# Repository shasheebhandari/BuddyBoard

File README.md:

Buddy Board

**Background**

When i was a kind my dad bought me one buddy toy , it had a screen , and a speaker that used to be activated when it was shaken . I was deeply connected to that toy but it got damaged later and i couldn't repair it . So In this project i have tried to re create that toy which used to display animation in idle but when shaken it used to show time . I am making this project to revive my childhood's fav toy buddy .

**Overview**

Buddy Board is a compact, ESP32-S3-based development board designed for projects requiring multi-USB connectivity, onboard sensing, and power management. The board integrates USB-C interfaces, an OLED display, motion and environmental sensors, and regulated power rails for both battery and USB-powered operation.

The design targets small-scale IoT or embedded applications where data acquisition, display, and connectivity need to coexist within a single board.

---

## Features
- **Microcontroller:** ESP32-S3-WROOM-1 with integrated WiFi and Bluetooth  
- **Display:** SSD1306 0.96" OLED module  
- **Sensors:**
  - BME680 (Gas, Temperature, Humidity, Pressure)
  - MPU-6000 (6-axis Accelerometer + Gyroscope)
- **USB Connectivity:**
  - 1x Upstream USB-C port (data and power input)
  - 2x Downstream USB-C ports (power and peripheral extension)
- **Power Management:**
  - TP4056-based Li-ion charging circuit
  - XL1509-3.3 buck converter for regulated 3.3V output
  - Screw terminal for external power or battery input
- **Indicator & Protection:**
  - SS34 Schottky diodes for reverse-current protection
  - Bypass and decoupling capacitors for power stability  

---

## Design Specifications
| Category | Specification |
|-----------|----------------|
| **MCU** | ESP32-S3-WROOM-1 |
| **Input Voltage** | 5V via USB or screw terminal |
| **Regulated Output** | 3.3V (via XL1509) |
| **Charging IC** | TP4056-42 ESOP8 |
| **Display Interface** | I²C (SDA, SCL) |
| **Sensor Interface** | I²C shared bus |
| **Board Layers** | 4 (Top, GND, Power, Bottom) |
| **Mounting** | Standard headers and terminal block |
| **Design Software** | KiCad 9 |

---

## File Contents
| File | Description |
|------|--------------|
| `.pro` | KiCad project file |
| `.sch` | Schematic diagram |
| `.pcb` | PCB layout |
| `.bom` | Bill of Materials |
| `.wrl` | 3D model (board visualization) |

---

## Component Summary (BOM)
| Reference | Qty | Component | Description |
|------------|-----|------------|--------------|
| U1 | 1 | ESP32-S3-WROOM-1 | Main processor |
| U2 | 1 | MPU-6000 | Motion sensor |
| U3 | 1 | XL1509-3.3 | Buck regulator |
| U4 | 1 | BME680 | Environmental sensor |
| U5 | 1 | TP4056-42 | Li-ion charger |
| D1, D3 | 2 | SS34 | Schottky diodes |
| J1, J2 | 2 | USB-C (Downstream) | Peripheral connections |
| J3 | 1 | USB-C (Upstream) | Power and data input |
| J4 | 1 | Screw terminal | External power input |
| C1–C4 | 4 | Capacitors | Power filtering |
| R1–R4 | 4 | Resistors | Pull-ups / current limiting |
| Brd1 | 1 | SSD1306 | OLED display module |

Full component details including footprints and datasheets are available in the included BOM file.

---

## Electrical Design Overview

### Power Distribution
- **5V Input:** Received from upstream USB-C or screw terminal.  
- **Voltage Regulation:** 5V stepped down to 3.3V via **XL1509-3.3** for logic and sensors.  
- **Battery Charging:** **TP4056** manages Li-ion charging when external power is available.  
- **Diode Protection:** **SS34 diodes** prevent reverse current between power sources.  

### Communication Buses
- **I²C Bus:**  
  Shared between ESP32-S3, SSD1306, BME680, and MPU-6000.  
  SDA and SCL lines routed with balanced lengths and pull-up resistors.  

- **USB Data Lines:**  
  Upstream USB carries data to ESP32-S3; downstream ports provide peripheral connectivity and power distribution.  

---

## PCB Design and Layout
- **Layer Stack:**  
  1. Top Layer — Signal routing and components  
  2. Inner Layer 1 — Dedicated Ground Plane  
  3. Inner Layer 2 — 5V and 3.3V Power Plane  
  4. Bottom Layer — Secondary signal routing  

- **Grounding:**  
  Solid ground plane with multiple stitching vias for signal integrity.  

- **Routing Strategy:**  
  - Differential routing for USB data pairs  
  - Short, wide traces for power lines  
  - Decoupling capacitors placed near IC supply pins  

---

## Assembly Notes
1. Open project in **KiCad 9** and verify all footprints before manufacturing.  
2. Use **4-layer PCB fabrication** (1.6mm FR4, 1oz copper recommended).  
3. Solder **SMD components** first (U1–U5, D1–D3).  
4. Solder **through-hole components** and connectors afterward.  
5. Validate **5V and 3.3V** rails before connecting the ESP32 module.  

---

## Testing Procedure
1. Connect power via upstream USB-C or screw terminal.  
2. Verify regulated **3.3V output** at the ESP32 supply pin.  
3. Connect via USB to confirm serial communication with ESP32.  
4. Test **I²C communication** for BME680, MPU-6000, and OLED display.  
5. Check **battery charging** operation using TP4056 circuit.  

---

## Future Improvements
- Add test points for voltage and communication lines.  
- Integrate onboard LEDs for power and charging indicators.  
- Improve USB impedance control.  
- Add ESD protection arrays on USB lines.  

---

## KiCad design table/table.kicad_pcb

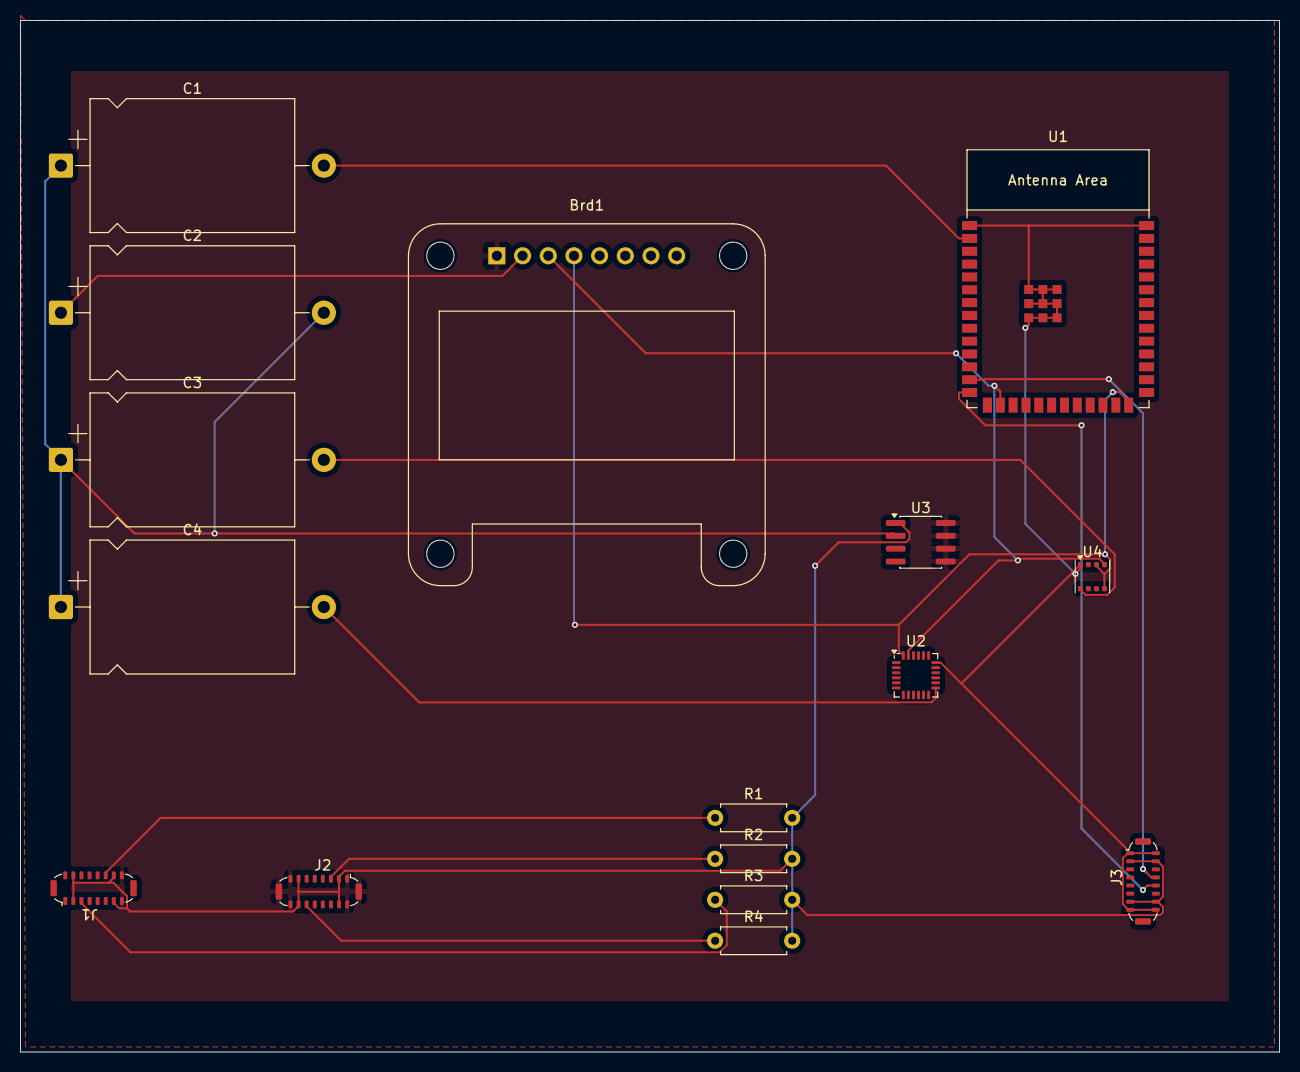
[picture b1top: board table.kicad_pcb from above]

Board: 2 copper layers, 124.5 x 102.0 mm, 16 parts (0 on the bottom side), 16 nets.

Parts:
Brd1: SSD1306; Adafruit_SSD1306
C1, C2, C3, C4: C; CP_Axial_L20.0mm_D13.0mm_P26.00mm_Horizontal
J1, J2: USB_C_Receptacle_down; USB_C_Plug_ShenzhenJingTuoJin_918-118A2021Y40002_Vertical
J3: USB_C_Receptacle_up; USB_C_Plug_ShenzhenJingTuoJin_918-118A2021Y40002_Vertical
R1, R2, R3, R4: R; R_Axial_DIN0207_L6.3mm_D2.5mm_P7.62mm_Horizontal
U1: ESP32-S3-WROOM-1
U2: MPU-6000; InvenSense_QFN-24_4x4mm_P0.5mm
U3: XL1509-3.3; SOIC-8_3.9x4.9mm_P1.27mm
U4: BME680; Bosch_LGA-8_3x3mm_P0.8mm_ClockwisePinNumbering

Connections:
unnamed: Brd1.1 (GND), J1.A1 (GND), J1.A12 (GND), J1.B1 (GND), J1.B12 (GND), J2.A1 (GND), J2.A12 (GND), J2.B1 (GND), J2.B12 (GND), J2.S1 (SHIELD), U3.5 (GND), U3.6 (GND), U3.7 (GND), U3.8 (GND)
unnamed: Brd1.3 (SCL), U1.16 (GPIO46), U2.23 (SCL/SCLK), U4.4 (SCK)
unnamed: Brd1.4 (SDA), U1.26 (GPIO45), U2.24 (SDA/MOSI), U4.3 (SDI), U4.5 (SDO)
unnamed: Brd1.2 (VCC), C2.1
unnamed: J1.A5 (CC1), R3.1
unnamed: J1.B5 (CC2), R1.1
unnamed: J2.A5 (CC1), R2.1
unnamed: J2.B5 (CC2), R4.1
unnamed: C1.2, U1.2 (3V3)
unnamed: J3.B7 (D-), U1.13 (GPIO19/U1RTS/ADC2_CH8/CLK_OUT2/USB_D-)
unnamed: J3.B6 (D+), U1.14 (GPIO20/U1CTS/ADC2_CH9/CLK_OUT1/USB_D+)
unnamed: J3.A1 (GND), J3.A12 (GND), J3.B1 (GND), J3.B12 (GND), U1.1 (GND), U1.40 (GND), U1.41 (GND), U2.18 (GND), U4.1 (GND)
unnamed: C4.2, U2.13 (VDD)
unnamed: C1.1, C2.2, C3.1, C4.1, U3.2 (OUT)
unnamed: J1.A4 (VBUS), J1.A9 (VBUS), J1.B4 (VBUS), J1.B9 (VBUS), J2.A4 (VBUS), J2.A9 (VBUS), J2.B4 (VBUS), J2.B9 (VBUS), J3.A4 (VBUS), J3.A9 (VBUS), J3.B4 (VBUS), J3.B9 (VBUS), R1.2, R2.2, R3.2, R4.2, U3.1 (VIN)
unnamed: C3.2, U4.8 (VDD)

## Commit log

2025-10-19 Rename Dazzling Snicket-Hango.stl to buddyboard.stl
2025-10-19 Rename table.csv to bom.csv
